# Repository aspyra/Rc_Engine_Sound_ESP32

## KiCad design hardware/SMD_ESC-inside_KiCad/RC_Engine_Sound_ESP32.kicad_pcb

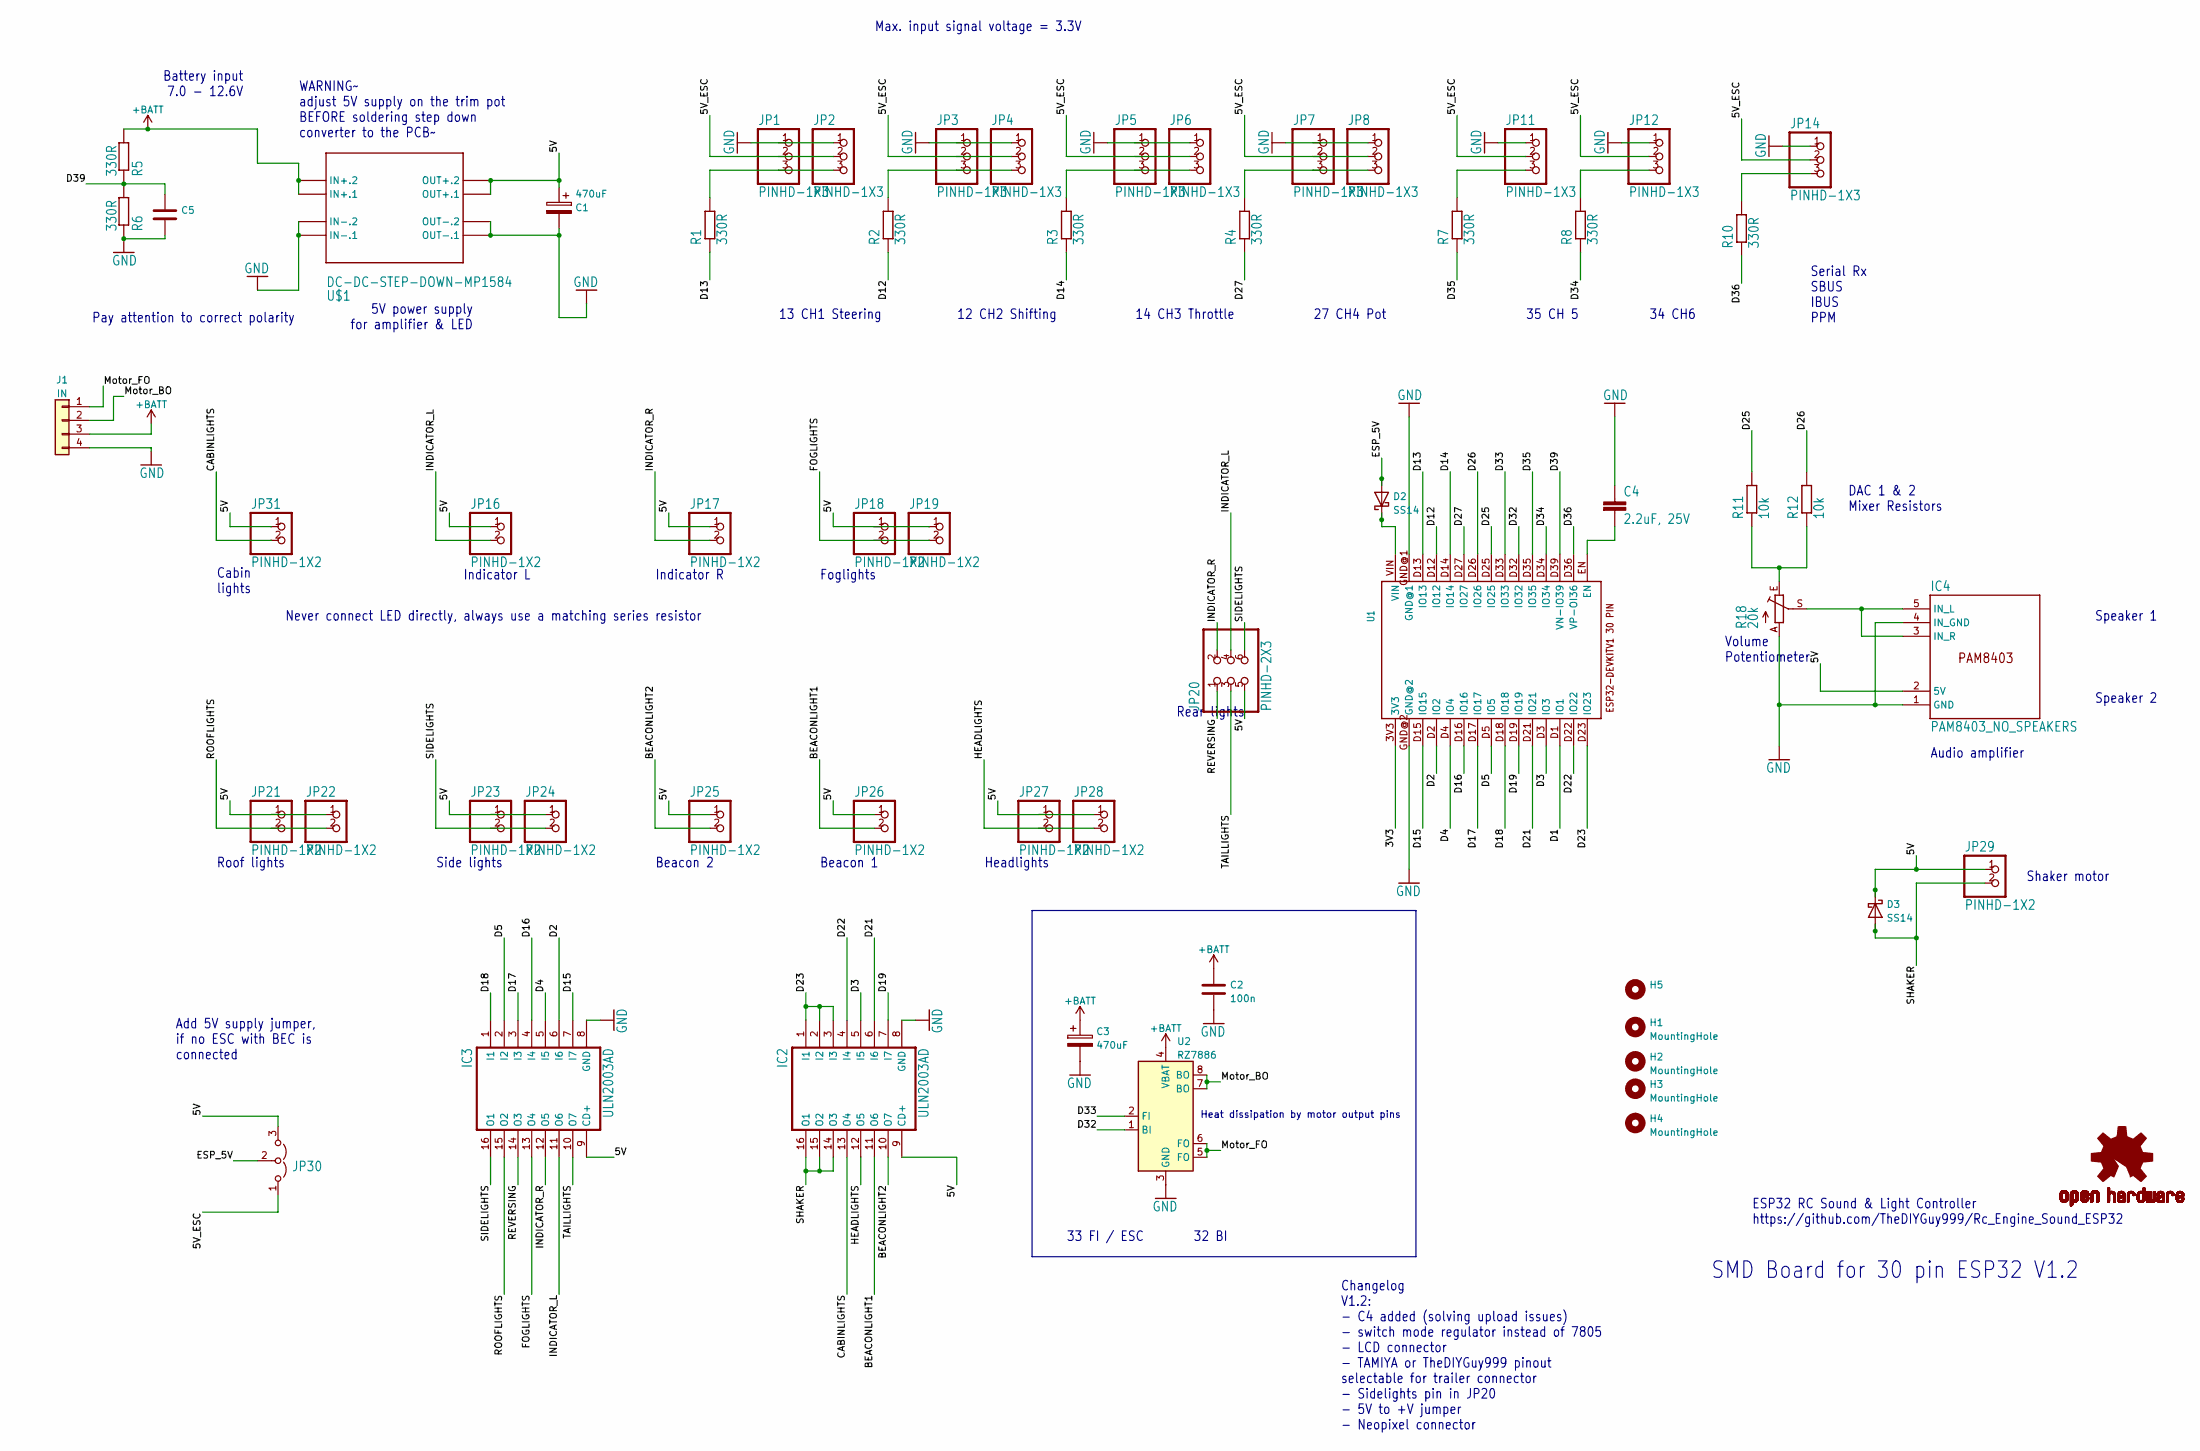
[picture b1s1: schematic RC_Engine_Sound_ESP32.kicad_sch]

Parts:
C1, C3: 470uF; CP_Radial_D10.0mm_P2.50mm_P5.00mm
C2: 100n; C_0603_1608Metric_Pad1.08x0.95mm_HandSolder
C4: 2.2uF, 25V; C_0805_2012Metric_Pad1.18x1.45mm_HandSolder
C5: C_0603_1608Metric_Pad1.08x0.95mm_HandSolder
D2, D3: SS14; D_SOD-123F
H1, H2, H3, H4: MountingHole; MountingHole_3.2mm_M3_DIN965
H5: (no value)
IC2, IC3: ULN2003AD; SO16
IC4: PAM8403_NO_SPEAKERS; PAM8403_SPEAKERS
J1: IN; TerminalBlock_Phoenix_PT-1,5-4-3.5-H_1x04_P3.50mm_Horizontal
JP1, JP2, JP3, JP4, JP5, JP6, JP7, JP8, JP11, JP12, JP14: PINHD-1X3; 1X03
JP16, JP17, JP18, JP19, JP21, JP22, JP23, JP24, JP25, JP26, JP27, JP28, JP29, JP31: PINHD-1X2; 1X02
JP20: PINHD-2X3; 2X03
JP30: (no value)
LOGO1: OSHW-LOGOM; OSHW-LOGO-M
R1, R2, R3, R4, R5, R6, R7, R8, R10: 330R; R_0603_1608Metric_Pad0.98x0.95mm_HandSolder
R11, R12: 10k; R_0603_1608Metric_Pad0.98x0.95mm_HandSolder
R18: 20k; S64W
U1: ESP32DEVKITV1; ESP32-DEVKITV1
U2: RZ7886; DIP-8_W7.62mm_LongPads
U$1: DC-DC-STEP-DOWN-MP1584

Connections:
+BATT: C2.1, C3.1, J1.3, R5.2, U2.4 (VBAT), U$1.IN+.1, U$1.IN+.2
/3V3: U1.3V3
/5V: C1.1, D3.1 (K), IC2.9 (CD+), IC3.9 (CD+), IC4.2 (5V), JP16.1, JP17.1, JP18.1, JP19.1, JP20.5, JP21.1, JP22.1, JP23.1, JP24.1, JP25.1, JP26.1, JP27.1, JP28.1, JP29.1, JP30.3 (B), JP31.1, U$1.OUT+.1, U$1.OUT+.2
/5V_ESC: JP1.2, JP2.2, JP3.2, JP4.2, JP5.2, JP6.2, JP7.2, JP8.2, JP11.2, JP12.2, JP14.2, JP30.1 (A)
/BEACONLIGHT1: IC2.11 (O6), JP26.2
/BEACONLIGHT2: IC2.10 (O7), JP25.2
/CABINLIGHTS: IC2.13 (O4), JP31.2
/D1: U1.D1 (IO1)
/D2: IC3.6 (I6), U1.D2 (IO2)
/D3: IC2.5 (I5), U1.D3 (IO3)
/D4: IC3.5 (I5), U1.D4 (IO4)
/D5: IC3.2 (I2), U1.D5 (IO5)
/D12: R2.1, U1.D12 (IO12)
/D13: R1.1, U1.D13 (IO13)
/D14: R3.1, U1.D14 (IO14)
/D15: IC3.7 (I7), U1.D15 (IO15)
/D16: IC3.4 (I4), U1.D16 (IO16)
/D17: IC3.3 (I3), U1.D17 (IO17)
/D18: IC3.1 (I1), U1.D18 (IO18)
/D19: IC2.7 (I7), U1.D19 (IO19)
/D21: IC2.6 (I6), U1.D21 (IO21)
/D22: IC2.4 (I4), U1.D22 (IO22)
/D23: IC2.1 (I1), IC2.2 (I2), IC2.3 (I3), U1.D23 (IO23)
/D25: R11.2, U1.D25 (IO25)
/D26: R12.2, U1.D26 (IO26)
/D27: R4.1, U1.D27 (IO27)
/D32: U1.D32 (IO32), U2.1 (BI)
/D33: U1.D33 (IO33), U2.2 (FI)
/D34: R8.1, U1.D34 (IO34)
/D35: R7.1, U1.D35 (IO35)
/D36: R10.1, U1.D36 (VP-OI36)
/D39: C5.1, R5.1, R6.2, U1.D39 (VN-IO39)
/ESP_5V: D2.2 (A), JP30.2 (C)
/FOGLIGHTS: IC3.13 (O4), JP18.2, JP19.2
/HEADLIGHTS: IC2.12 (O5), JP27.2, JP28.2
/INDICATOR_L: IC3.11 (O6), JP16.2, JP20.4
/INDICATOR_R: IC3.12 (O5), JP17.2, JP20.2
/Motor_BO: J1.2, U2.7 (BO), U2.8 (BO)
/Motor_FO: J1.1, U2.5 (FO), U2.6 (FO)
/REVERSING: IC3.14 (O3), JP20.1
/ROOFLIGHTS: IC3.15 (O2), JP21.2, JP22.2
/SHAKER: D3.2 (A), IC2.14 (O3), IC2.15 (O2), IC2.16 (O1), JP29.2
/SIDELIGHTS: IC3.16 (O1), JP20.6, JP23.2, JP24.2
/TAILLIGHTS: IC3.10 (O7), JP20.3
GND: C1.2, C2.2, C3.2, C4.1, C5.2, IC2.8 (GND), IC3.8 (GND), IC4.1 (GND), IC4.4 (IN_GND), J1.4, JP1.1, JP2.1, JP3.1, JP4.1, JP5.1, JP6.1, JP7.1, JP8.1, JP11.1, JP12.1, JP14.1, R6.1, R18.A, U1.GND@1, U1.GND@2, U2.3 (GND), U$1.IN-.1, U$1.IN-.2, U$1.OUT-.1, U$1.OUT-.2
unnamed: C4.2, U1.EN
unnamed: D2.1 (K), U1.VIN
unnamed: IC4.3 (IN_R), IC4.5 (IN_L), R18.S
unnamed: JP1.3, JP2.3, R1.2
unnamed: JP3.3, JP4.3, R2.2
unnamed: JP5.3, JP6.3, R3.2
unnamed: JP7.3, JP8.3, R4.2
unnamed: JP11.3, R7.2
unnamed: JP12.3, R8.2
unnamed: JP14.3, R10.2
unnamed: R11.1, R12.1, R18.E

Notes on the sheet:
Add 5V supply jumper, if no ESC with BEC is connected~{}
Indicator R
Volume Potentiometer
Shaker motor
35 CH 5
Rear lights
Cabin lights
Side lights
Heat dissipation by motor output pins
Max. input signal voltage = 3.3V~{}
Audio amplifier
Pay attention to correct polarity~{}
Foglights
32 BI
13 CH1 Steering
Speaker 2
Beacon 1
Serial Rx SBUS IBUS PPM
Never connect LED directly, always use a matching series resistor~{}
SMD Board for 30 pin ESP32 V1.2
DAC 1 & 2 Mixer Resistors
14 CH3 Throttle
Headlights
5V power supply for amplifier & LED
ESP32 RC Sound & Light Controller https://github.com/TheDIYGuy999/Rc_Engine_Sound_ESP32
Battery input 7.0 - 12.6V
27 CH4 Pot
34 CH6
Beacon 2
Roof lights
33 FI / ESC
WARNING~ adjust 5V supply on the trim pot BEFORE soldering step down converter to the PCB~
12 CH2 Shifting
Changelog V1.2: - C4 added (solving upload issues) - switch mode regulator instead of 7805 - LCD connector - TAMIYA or TheDIYGuy999 pinout selectable for trailer connector - Sidelights pin in JP20 - 5V to +V jumper - Neopixel connector
Indicator L
Speaker 1

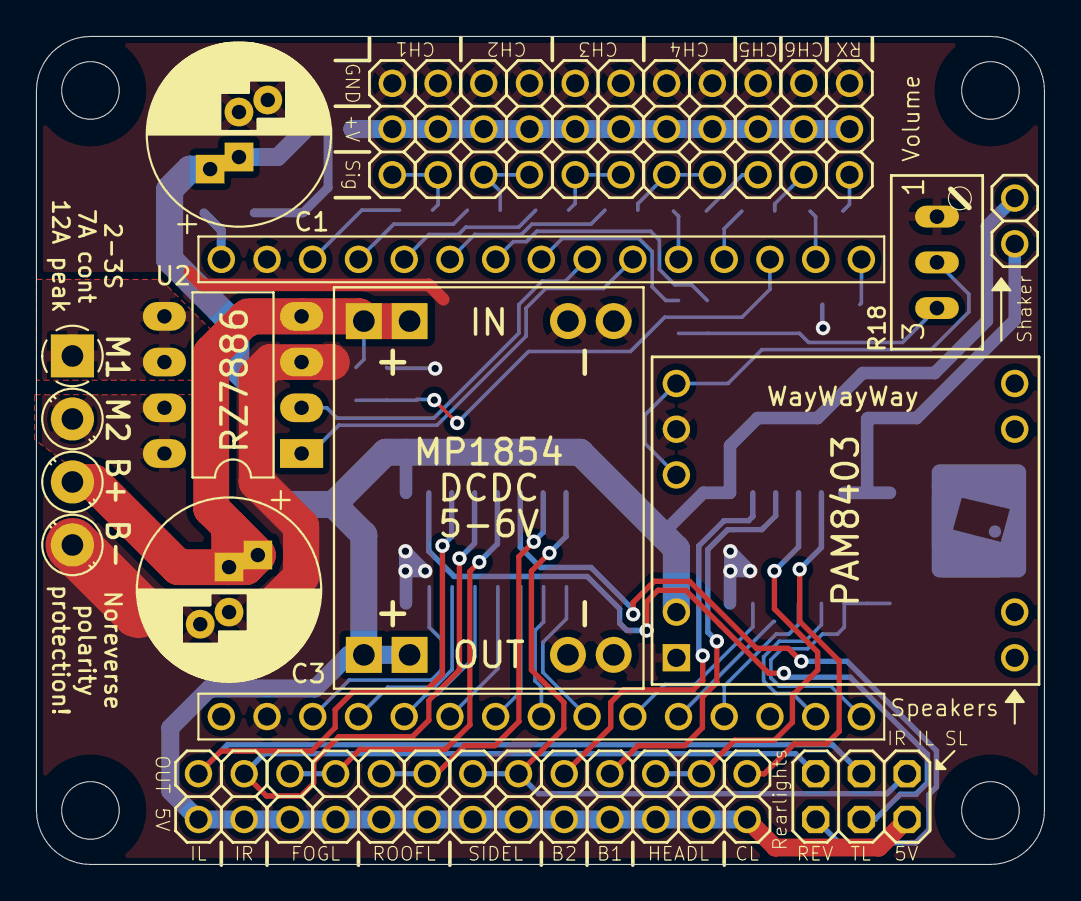
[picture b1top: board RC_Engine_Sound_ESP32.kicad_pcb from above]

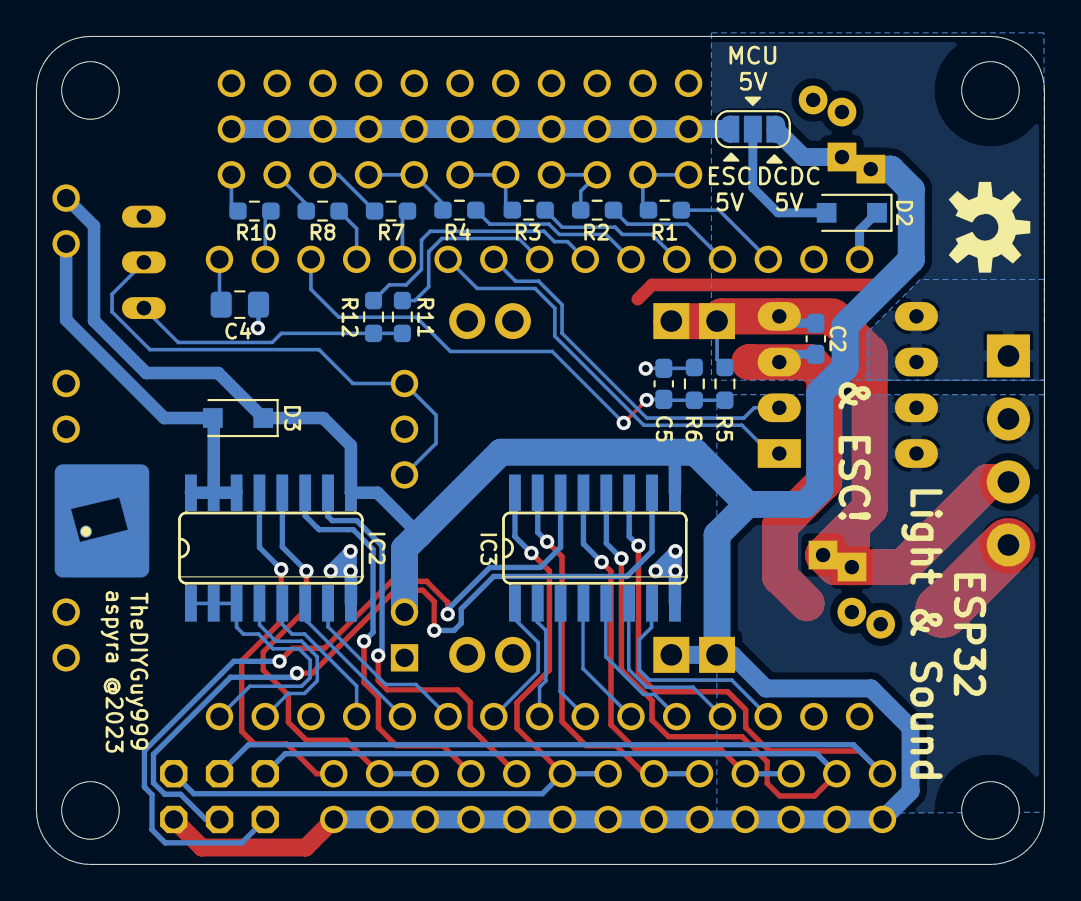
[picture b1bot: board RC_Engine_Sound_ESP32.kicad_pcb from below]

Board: 2 copper layers, 56.0 x 46.0 mm, 59 parts (21 on the bottom side), 54 nets.

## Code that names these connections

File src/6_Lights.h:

#include <Arduino.h>

/* General LIGHTS SETTINGS ***********************************************************************************************************************
 *  
 * Most lights settings are done in the vehicle configuration files in the /vehicles/ directory.
 * 
 */

// Neopixel settings ----------------------------------------------------------------------------------------------------------------------------- 
//#define NEOPIXEL_ENABLED // GPIO0 used for WS2812 Neopixel control, if defined!
#define NEOPIXEL_COUNT 8 // How many Neopixels? 8 for Knight Rider, 3 for B33lz3bub
#define NEOPIXEL_BRIGHTNESS  127 // Brightness (255 is the maximum)
#define MAX_POWER_MILLIAMPS 100 // Maximum allowed current draw in mA (100 recommended, depending on your 5V supply)

// Choose the animation you want
//#define NEOPIXEL_DEMO // Demo
//#define NEOPIXEL_KNIGHT_RIDER // Knight Rider scanner animation for 8 LED (use it in combination with "kittScanner.h" "siren" sound in your vehicle file)
#define NEOPIXEL_BLUELIGHT // Bluelight animation for 8 LED
//#define NEOPIXEL_UNION_JACK // United Kingdom animation for 8 LED (use it in combination with "BritishNationalAnthemSiren.h" sound in your vehicle file)
#define NEOPIXEL_HIGHBEAM // Neopixel bar is used as high beam as well, if defined. Also usable in combination with NEOPIXEL_KNIGHT_RIDER & NEOPIXEL_BLUELIGHT
//#define NEOPIXEL_B33LZ3BUB // B33lz3bub Austria animation for 3 LED: https://www.rc-modellbau-portal.de/index.php?threads/baubericht-mercedes-actros-1851-gigaspace-tamiya.14349/page-3


// The following options may already be defined in the vehicle file. Don't uncomment them in this case or you will get a redefinition error ------
//#define XENON_LIGHTS // Headlights will show a xenon bulb ignition flash, if defined
//#define SEPARATE_FULL_BEAM // The full beam is a separate bulb, connected to roof lights pin. Connect roof lights to side lights in this case
//#define INDICATOR_SIDE_MARKERS // The indicators are used as side markers as well. This is commonly used in US trucks.

// More light configurations ---------------------------------------------------------------------------------------------------------------------
//#define NO_CABLIGHTS // The cablights step in the lights sequence is skipped, if defined
//#define NO_FOGLIGHTS // The foglights step in the lights sequence is skipped, if defined
//#define THIRD_BRAKELIGHT // if defined, pin 32 is used for a third brake light, otherwise for a trailer presence switch (pulled to GND = no trailer attached)
//#define FLICKERING_WHILE_CRANKING // The lights will flicker a bit during engine cranking, otherwise they are just a bit dimmed
//#define HAZARDS_WHILE_5TH_WHEEL_UNLOCKED // Hazards on, if 5th wheel is unlocked

// Adjust the brightness of your lights here -----------------------------------------------------------------------------------------------------
// All brightness values 0 - 255
uint8_t cabLightsBrightness = 100; // Usually 255, 100 for Actros & Ural
uint8_t sideLightsBrightness = 150; // Usually 200, 100 for WPL C44, 50 for Landy, 100 for P407, 150 for Actros
uint8_t rearlightDimmedBrightness = 30; // tailligt brightness, if not braking, about 30
uint8_t rearlightParkingBrightness = 3; // 0, if you want the taillights being off, if side lights are on, or about 5 if you want them on (0 for US Mode)
uint8_t headlightParkingBrightness = 3; // 0, if you want the headlights being off, if side lights are on, or about 5 if you want them on (0 for US Mode)
uint8_t reversingLightBrightness = 140; // Around 140, 50 for Landy & Ural

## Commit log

2023-11-29 Added hardware variant with built-in ESC
2023-11-29 Updated some options to match WPL B16 (PWM receiver)
2023-11-29 Fixed file names
2023-12-01 Downgraded ESP-IDF version to 3.0.0 in platformio.ini to match ESP32 board def v1.0.4 in Arduino IDE. Temporarily removed ESP32AnalogRead use because it doesn't work with 3.0.0 / v1.0.4.
2023-12-01 Added Bluepad32 "Controller" example into src.ino
